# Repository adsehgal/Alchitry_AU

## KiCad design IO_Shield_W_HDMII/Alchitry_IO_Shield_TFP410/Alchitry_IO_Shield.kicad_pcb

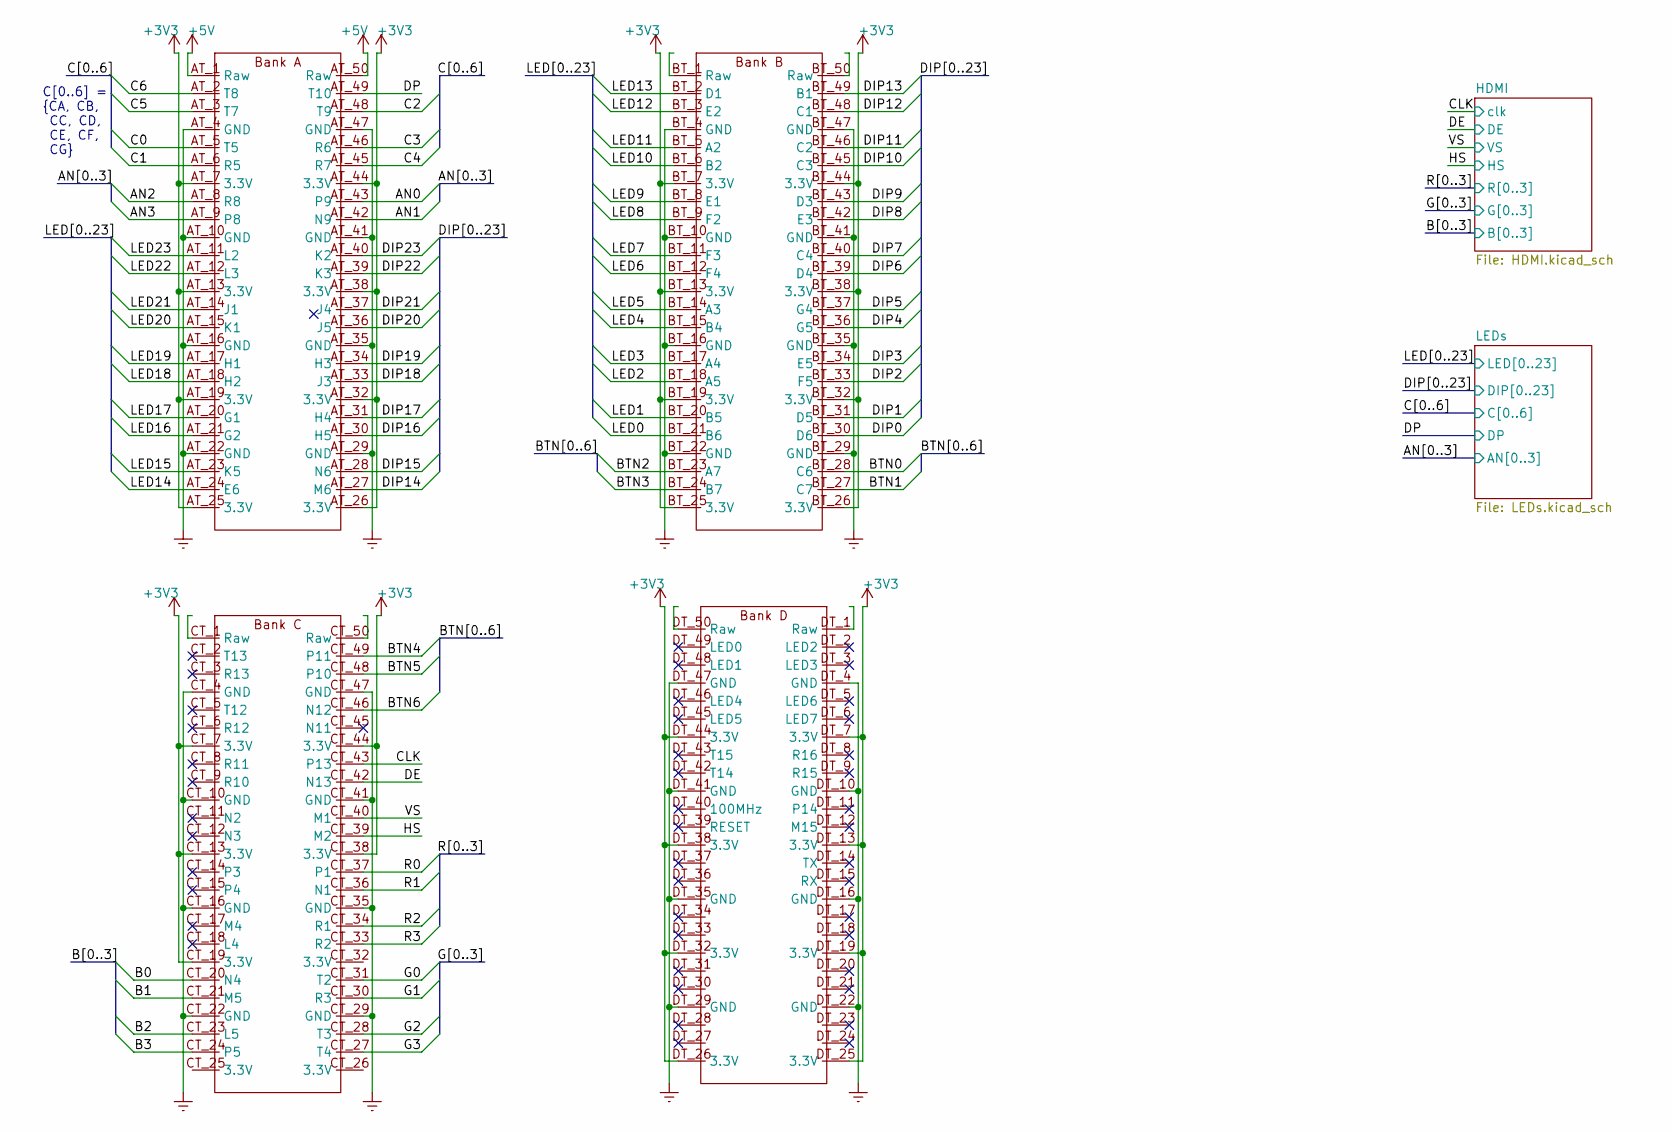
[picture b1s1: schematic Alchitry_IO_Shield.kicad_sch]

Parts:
U0: boardmezzanine_new; Alchitry_Top_Bottom

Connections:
+3V3: U0.AB_7, U0.AB_13, U0.AB_19, U0.AB_25, U0.AB_26, U0.AB_32, U0.AB_38, U0.AB_44, U0.AT_7 (3.3V), U0.AT_13 (3.3V), U0.AT_19 (3.3V), U0.AT_25 (3.3V), U0.AT_26 (3.3V), U0.AT_32 (3.3V), U0.AT_38 (3.3V), U0.AT_44 (3.3V), U0.BB_7, U0.BB_13, U0.BB_19, U0.BB_25, U0.BB_26, U0.BB_32, U0.BB_38, U0.BB_44, U0.BT_7 (3.3V), U0.BT_13 (3.3V), U0.BT_19 (3.3V), U0.BT_25 (3.3V), U0.BT_26 (3.3V), U0.BT_32 (3.3V), U0.BT_38 (3.3V), U0.BT_44 (3.3V), U0.CB_7, U0.CB_13, U0.CB_19, U0.CB_38, U0.CB_44, U0.CT_7 (3.3V), U0.CT_13 (3.3V), U0.CT_19 (3.3V), U0.CT_38 (3.3V), U0.CT_44 (3.3V), U0.DB_7, U0.DB_13, U0.DB_19, U0.DB_25, U0.DB_26, U0.DB_32, U0.DB_38, U0.DB_44, U0.DT_7 (3.3V), U0.DT_13 (3.3V), U0.DT_19 (3.3V), U0.DT_25 (3.3V), U0.DT_26 (3.3V), U0.DT_32 (3.3V), U0.DT_38 (3.3V), U0.DT_44 (3.3V); also elsewhere on the board
+5V: U0.AB_1, U0.AB_50, U0.AT_1 (Raw), U0.AT_50 (Raw); also elsewhere on the board
/AN0: U0.AB_43, U0.AT_43 (P9); also elsewhere on the board
/AN1: U0.AB_42, U0.AT_42 (N9); also elsewhere on the board
/AN2: U0.AB_8, U0.AT_8 (R8); also elsewhere on the board
/AN3: U0.AB_9, U0.AT_9 (P8); also elsewhere on the board
/B0: U0.CB_20, U0.CT_20 (N4); also elsewhere on the board
/B1: U0.CB_21, U0.CT_21 (M5); also elsewhere on the board
/B2: U0.CB_23, U0.CT_23 (L5); also elsewhere on the board
/B3: U0.CB_24, U0.CT_24 (P5); also elsewhere on the board
/BTN0: U0.BB_28, U0.BT_28 (C6)
/BTN1: U0.BB_27, U0.BT_27 (C7)
/BTN2: U0.BB_23, U0.BT_23 (A7)
/BTN3: U0.BB_24, U0.BT_24 (B7)
/BTN4: U0.CB_49, U0.CT_49 (P11)
/BTN5: U0.CB_48, U0.CT_48 (P10)
/BTN6: U0.CB_46, U0.CT_46 (N12)
/C0: U0.AB_5, U0.AT_5 (T5); also elsewhere on the board
/C1: U0.AB_6, U0.AT_6 (R5); also elsewhere on the board
/C2: U0.AB_48, U0.AT_48 (T9); also elsewhere on the board
/C3: U0.AB_46, U0.AT_46 (R6); also elsewhere on the board
/C4: U0.AB_45, U0.AT_45 (R7); also elsewhere on the board
/C5: U0.AB_3, U0.AT_3 (T7); also elsewhere on the board
/C6: U0.AB_2, U0.AT_2 (T8); also elsewhere on the board
/CLK: U0.CB_43, U0.CT_43 (P13); also elsewhere on the board
/DE: U0.CB_42, U0.CT_42 (N13); also elsewhere on the board
/DIP0: U0.BB_30, U0.BT_30 (D6); also elsewhere on the board
/DIP1: U0.BB_31, U0.BT_31 (D5); also elsewhere on the board
/DIP2: U0.BB_33, U0.BT_33 (F5); also elsewhere on the board
/DIP3: U0.BB_34, U0.BT_34 (E5); also elsewhere on the board
/DIP4: U0.BB_36, U0.BT_36 (G5); also elsewhere on the board
/DIP5: U0.BB_37, U0.BT_37 (G4); also elsewhere on the board
/DIP6: U0.BB_39, U0.BT_39 (D4); also elsewhere on the board
/DIP7: U0.BB_40, U0.BT_40 (C4); also elsewhere on the board
/DIP8: U0.BB_42, U0.BT_42 (E3); also elsewhere on the board
/DIP9: U0.BB_43, U0.BT_43 (D3); also elsewhere on the board
/DIP10: U0.BB_45, U0.BT_45 (C3); also elsewhere on the board
/DIP11: U0.BB_46, U0.BT_46 (C2); also elsewhere on the board
/DIP12: U0.BB_48, U0.BT_48 (C1); also elsewhere on the board
/DIP13: U0.BB_49, U0.BT_49 (B1); also elsewhere on the board
/DIP14: U0.AB_27, U0.AT_27 (M6); also elsewhere on the board
/DIP15: U0.AB_28, U0.AT_28 (N6); also elsewhere on the board
/DIP16: U0.AB_30, U0.AT_30 (H5); also elsewhere on the board
/DIP17: U0.AB_31, U0.AT_31 (H4); also elsewhere on the board
/DIP18: U0.AB_33, U0.AT_33 (J3); also elsewhere on the board
/DIP19: U0.AB_34, U0.AT_34 (H3); also elsewhere on the board
/DIP20: U0.AB_36, U0.AT_36 (J5); also elsewhere on the board
/DIP21: U0.AB_37, U0.AT_37 (J4); also elsewhere on the board
/DIP22: U0.AB_39, U0.AT_39 (K3); also elsewhere on the board
/DIP23: U0.AB_40, U0.AT_40 (K2); also elsewhere on the board
/DP: U0.AB_49, U0.AT_49 (T10)
/G0: U0.CB_31, U0.CT_31 (T2); also elsewhere on the board
/G1: U0.CB_30, U0.CT_30 (R3); also elsewhere on the board
/G2: U0.CB_28, U0.CT_28 (T3); also elsewhere on the board
/G3: U0.CB_27, U0.CT_27 (T4); also elsewhere on the board
/HS: U0.CB_39, U0.CT_39 (M2); also elsewhere on the board
/LED0: U0.BB_21, U0.BT_21 (B6); also elsewhere on the board
/LED1: U0.BB_20, U0.BT_20 (B5); also elsewhere on the board
/LED2: U0.BB_18, U0.BT_18 (A5); also elsewhere on the board
/LED3: U0.BB_17, U0.BT_17 (A4); also elsewhere on the board
/LED4: U0.BB_15, U0.BT_15 (B4); also elsewhere on the board
/LED5: U0.BB_14, U0.BT_14 (A3); also elsewhere on the board
/LED6: U0.BB_12, U0.BT_12 (F4); also elsewhere on the board
/LED7: U0.BB_11, U0.BT_11 (F3); also elsewhere on the board
/LED8: U0.BB_9, U0.BT_9 (F2); also elsewhere on the board
/LED9: U0.BB_8, U0.BT_8 (E1); also elsewhere on the board
/LED10: U0.BB_6, U0.BT_6 (B2); also elsewhere on the board
/LED11: U0.BB_5, U0.BT_5 (A2); also elsewhere on the board
/LED12: U0.BB_3, U0.BT_3 (E2); also elsewhere on the board
/LED13: U0.BB_2, U0.BT_2 (D1); also elsewhere on the board
/LED14: U0.AB_24, U0.AT_24 (E6); also elsewhere on the board
/LED15: U0.AB_23, U0.AT_23 (K5); also elsewhere on the board
/LED16: U0.AB_21, U0.AT_21 (G2); also elsewhere on the board
/LED17: U0.AB_20, U0.AT_20 (G1); also elsewhere on the board
/LED18: U0.AB_18, U0.AT_18 (H2); also elsewhere on the board
/LED19: U0.AB_17, U0.AT_17 (H1); also elsewhere on the board
/LED20: U0.AB_15, U0.AT_15 (K1); also elsewhere on the board
/LED21: U0.AB_14, U0.AT_14 (J1); also elsewhere on the board
/LED22: U0.AB_12, U0.AT_12 (L3); also elsewhere on the board
/LED23: U0.AB_11, U0.AT_11 (L2); also elsewhere on the board
/R0: U0.CB_37, U0.CT_37 (P1); also elsewhere on the board
/R1: U0.CB_36, U0.CT_36 (N1); also elsewhere on the board
/R2: U0.CB_34, U0.CT_34 (R1); also elsewhere on the board
/R3: U0.CB_33, U0.CT_33 (R2); also elsewhere on the board
/VS: U0.CB_40, U0.CT_40 (M1); also elsewhere on the board
GNDREF: U0.AB_4, U0.AB_10, U0.AB_16, U0.AB_22, U0.AB_29, U0.AB_35, U0.AB_41, U0.AB_47, U0.AT_4 (GND), U0.AT_10 (GND), U0.AT_16 (GND), U0.AT_22 (GND), U0.AT_29 (GND), U0.AT_35 (GND), U0.AT_41 (GND), U0.AT_47 (GND), U0.BB_4, U0.BB_10, U0.BB_16, U0.BB_22, U0.BB_29, U0.BB_35, U0.BB_41, U0.BB_47, U0.BT_4 (GND), U0.BT_10 (GND), U0.BT_16 (GND), U0.BT_22 (GND), U0.BT_29 (GND), U0.BT_35 (GND), U0.BT_41 (GND), U0.BT_47 (GND), U0.CB_4, U0.CB_10, U0.CB_16, U0.CB_22, U0.CB_29, U0.CB_35, U0.CB_41, U0.CB_47, U0.CT_4 (GND), U0.CT_10 (GND), U0.CT_16 (GND), U0.CT_22 (GND), U0.CT_29 (GND), U0.CT_35 (GND), U0.CT_41 (GND), U0.CT_47 (GND), U0.DB_4, U0.DB_10, U0.DB_16, U0.DB_22, U0.DB_29, U0.DB_35, U0.DB_41, U0.DB_47, U0.DT_4 (GND), U0.DT_10 (GND), U0.DT_16 (GND), U0.DT_22 (GND), U0.DT_29 (GND), U0.DT_35 (GND), U0.DT_41 (GND), U0.DT_47 (GND); also elsewhere on the board
unnamed: U0.BB_1, U0.BT_1 (Raw)
unnamed: U0.BB_50, U0.BT_50 (Raw)
unnamed: U0.CB_1, U0.CT_1 (Raw)
unnamed: U0.CB_2, U0.CT_2 (T13)
unnamed: U0.CB_3, U0.CT_3 (R13)
unnamed: U0.CB_5, U0.CT_5 (T12)
unnamed: U0.CB_6, U0.CT_6 (R12)
unnamed: U0.CB_8, U0.CT_8 (R11)
unnamed: U0.CB_9, U0.CT_9 (R10)
unnamed: U0.CB_11, U0.CT_11 (N2)
unnamed: U0.CB_12, U0.CT_12 (N3)
unnamed: U0.CB_14, U0.CT_14 (P3)
unnamed: U0.CB_15, U0.CT_15 (P4)
unnamed: U0.CB_17, U0.CT_17 (M4)
unnamed: U0.CB_18, U0.CT_18 (L4)
unnamed: U0.CB_25, U0.CT_25 (3.3V)
unnamed: U0.CB_26, U0.CT_26 (3.3V)
unnamed: U0.CB_32, U0.CT_32 (3.3V)
unnamed: U0.CB_45, U0.CT_45 (N11)
unnamed: U0.CB_50, U0.CT_50 (Raw)
unnamed: U0.DB_1, U0.DT_1 (Raw)
unnamed: U0.DB_2, U0.DT_2 (LED2)
unnamed: U0.DB_3, U0.DT_3 (LED3)
unnamed: U0.DB_5, U0.DT_5 (LED6)
unnamed: U0.DB_6, U0.DT_6 (LED7)
unnamed: U0.DB_8, U0.DT_8 (R16)
unnamed: U0.DB_9, U0.DT_9 (R15)
unnamed: U0.DB_11, U0.DT_11 (P14)
unnamed: U0.DB_12, U0.DT_12 (M15)
unnamed: U0.DB_14, U0.DT_14 (TX)
unnamed: U0.DB_15, U0.DT_15 (RX)
unnamed: U0.DB_17, U0.DT_17
unnamed: U0.DB_18, U0.DT_18
unnamed: U0.DB_20, U0.DT_20
unnamed: U0.DB_21, U0.DT_21
unnamed: U0.DB_23, U0.DT_23
unnamed: U0.DB_24, U0.DT_24
unnamed: U0.DB_27, U0.DT_27
unnamed: U0.DB_28, U0.DT_28
unnamed: U0.DB_30, U0.DT_30
unnamed: U0.DB_31, U0.DT_31
unnamed: U0.DB_33, U0.DT_33
unnamed: U0.DB_34, U0.DT_34
unnamed: U0.DB_36, U0.DT_36
unnamed: U0.DB_37, U0.DT_37
unnamed: U0.DB_39, U0.DT_39 (RESET)
unnamed: U0.DB_40, U0.DT_40 (100MHz)
unnamed: U0.DB_42, U0.DT_42 (T14)
unnamed: U0.DB_43, U0.DT_43 (T15)
unnamed: U0.DB_45, U0.DT_45 (LED5)
unnamed: U0.DB_46, U0.DT_46 (LED4)
unnamed: U0.DB_48, U0.DT_48 (LED1)
unnamed: U0.DB_49, U0.DT_49 (LED0)
unnamed: U0.DB_50, U0.DT_50 (Raw)

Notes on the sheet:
C[0..6] = {CA, CB, CC, CD, CE, CF, CG}

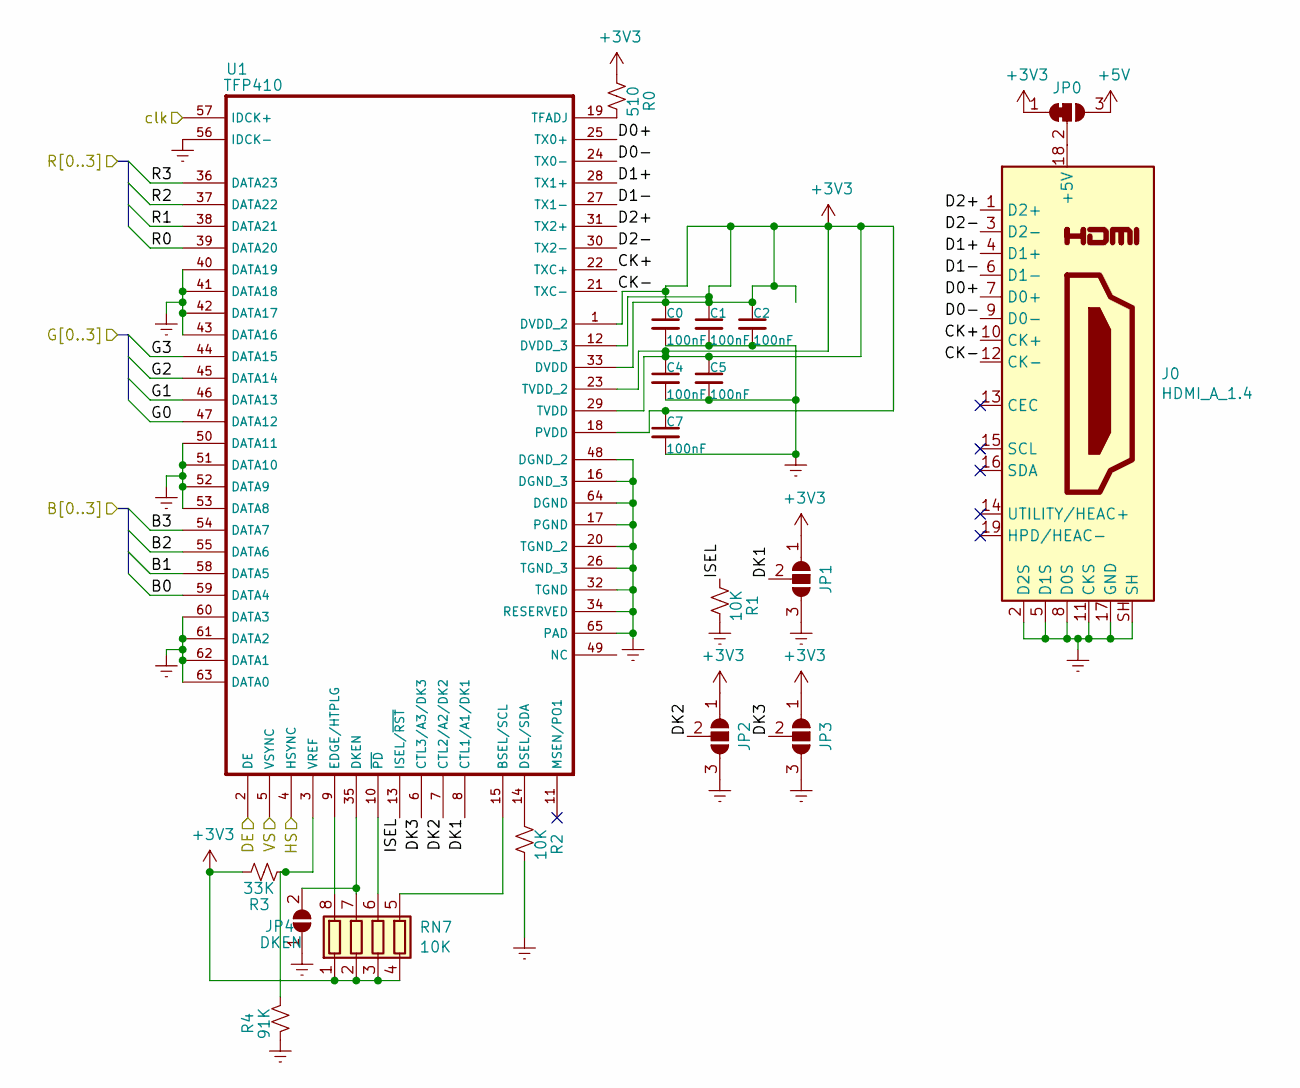
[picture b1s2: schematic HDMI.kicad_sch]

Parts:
C0, C1, C2, C4, C5, C7: 100nF; C_0603_1608Metric_Pad1.05x0.95mm_HandSolder
J0: HDMI_A_1.4; HDMI
JP0: V_Sel; jumper_1_2_bridged
JP1: DK1; jumper_unbridged
JP2: DK2; jumper_unbridged
JP3: DK3; jumper_unbridged
JP4: DKEN; Jumper_2_Pin_Unbridged
R0: 510; R_0603_1608Metric_Pad1.05x0.95mm_HandSolder
R1, R2: 10K; R_0603_1608Metric
R3: 33K; R_0603_1608Metric
R4: 91K; R_0603_1608Metric
RN7: 10K; R_Array_Concave_4x0603
U1: TFP410; HTQFP-64-1EP_10x10mm_P0.5mm_EP8x8mm_Mask4.4x4.4mm_ThermalVi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

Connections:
+3V3: C0.1, C1.1, C2.1, C4.1, C5.1, C7.1, JP0.1 (A), JP1.1 (A), JP2.1 (A), JP3.1 (A), R0.1, R3.2, RN7.1 (R1.1), RN7.2 (R2.1), RN7.3 (R3.1), RN7.4 (R4.1), U1.1 (DVDD_2), U1.12 (DVDD_3), U1.18 (PVDD), U1.23 (TVDD_2), U1.29 (TVDD), U1.33 (DVDD); also elsewhere on the board
+5V: JP0.3 (B); also elsewhere on the board
/B0: U1.59 (DATA4); also elsewhere on the board
/B1: U1.58 (DATA5); also elsewhere on the board
/B2: U1.55 (DATA6); also elsewhere on the board
/B3: U1.54 (DATA7); also elsewhere on the board
/CLK: U1.57 (IDCK+); also elsewhere on the board
/DE: U1.2 (DE); also elsewhere on the board
/G0: U1.47 (DATA12); also elsewhere on the board
/G1: U1.46 (DATA13); also elsewhere on the board
/G2: U1.45 (DATA14); also elsewhere on the board
/G3: U1.44 (DATA15); also elsewhere on the board
/HDMI/CK+: J0.10 (CK+), U1.22 (TXC+)
/HDMI/CK-: J0.12 (CK-), U1.21 (TXC-)
/HDMI/D0+: J0.7 (D0+), U1.25 (TX0+)
/HDMI/D0-: J0.9 (D0-), U1.24 (TX0-)
/HDMI/D1+: J0.4 (D1+), U1.28 (TX1+)
/HDMI/D1-: J0.6 (D1-), U1.27 (TX1-)
/HDMI/D2+: J0.1 (D2+), U1.31 (TX2+)
/HDMI/D2-: J0.3 (D2-), U1.30 (TX2-)
/HDMI/DK1: JP1.2 (C), U1.8 (CTL1/A1/DK1)
/HDMI/DK2: JP2.2 (C), U1.7 (CTL2/A2/DK2)
/HDMI/DK3: JP3.2 (C), U1.6 (CTL3/A3/DK3)
/HDMI/ISEL: R1.1, U1.13 (ISEL/~RST)
/HS: U1.4 (HSYNC); also elsewhere on the board
/R0: U1.39 (DATA20); also elsewhere on the board
/R1: U1.38 (DATA21); also elsewhere on the board
/R2: U1.37 (DATA22); also elsewhere on the board
/R3: U1.36 (DATA23); also elsewhere on the board
/VS: U1.5 (VSYNC); also elsewhere on the board
GNDREF: C0.2, C1.2, C2.2, C4.2, C5.2, C7.2, J0.2 (D2S), J0.5 (D1S), J0.8 (D0S), J0.11 (CKS), J0.17 (GND), J0.SH, JP1.3 (B), JP2.3 (B), JP3.3 (B), JP4.1 (A), R1.2, R2.2, R4.2, U1.16 (DGND_3), U1.17 (PGND), U1.20 (TGND_2), U1.26 (TGND_3), U1.32 (TGND), U1.34 (RESERVED), U1.40 (DATA19), U1.41 (DATA18), U1.42 (DATA17), U1.43 (DATA16), U1.48 (DGND_2), U1.50 (DATA11), U1.51 (DATA10), U1.52 (DATA9), U1.53 (DATA8), U1.56 (IDCK-), U1.60 (DATA3), U1.61 (DATA2), U1.62 (DATA1), U1.63 (DATA0), U1.64 (DGND), U1.65 (PAD); also elsewhere on the board
unnamed: J0.18 (+5V), JP0.2 (C)
unnamed: JP4.2 (B), RN7.7 (R2.2), U1.35 (DKEN)
unnamed: R0.2, U1.19 (TFADJ)
unnamed: R2.1, U1.14 (DSEL/SDA)
unnamed: R3.1, R4.1, U1.3 (VREF)
unnamed: RN7.5 (R4.2), U1.15 (BSEL/SCL)
unnamed: RN7.6 (R3.2), U1.10 (~PD)
unnamed: RN7.8 (R1.2), U1.9 (EDGE/HTPLG)

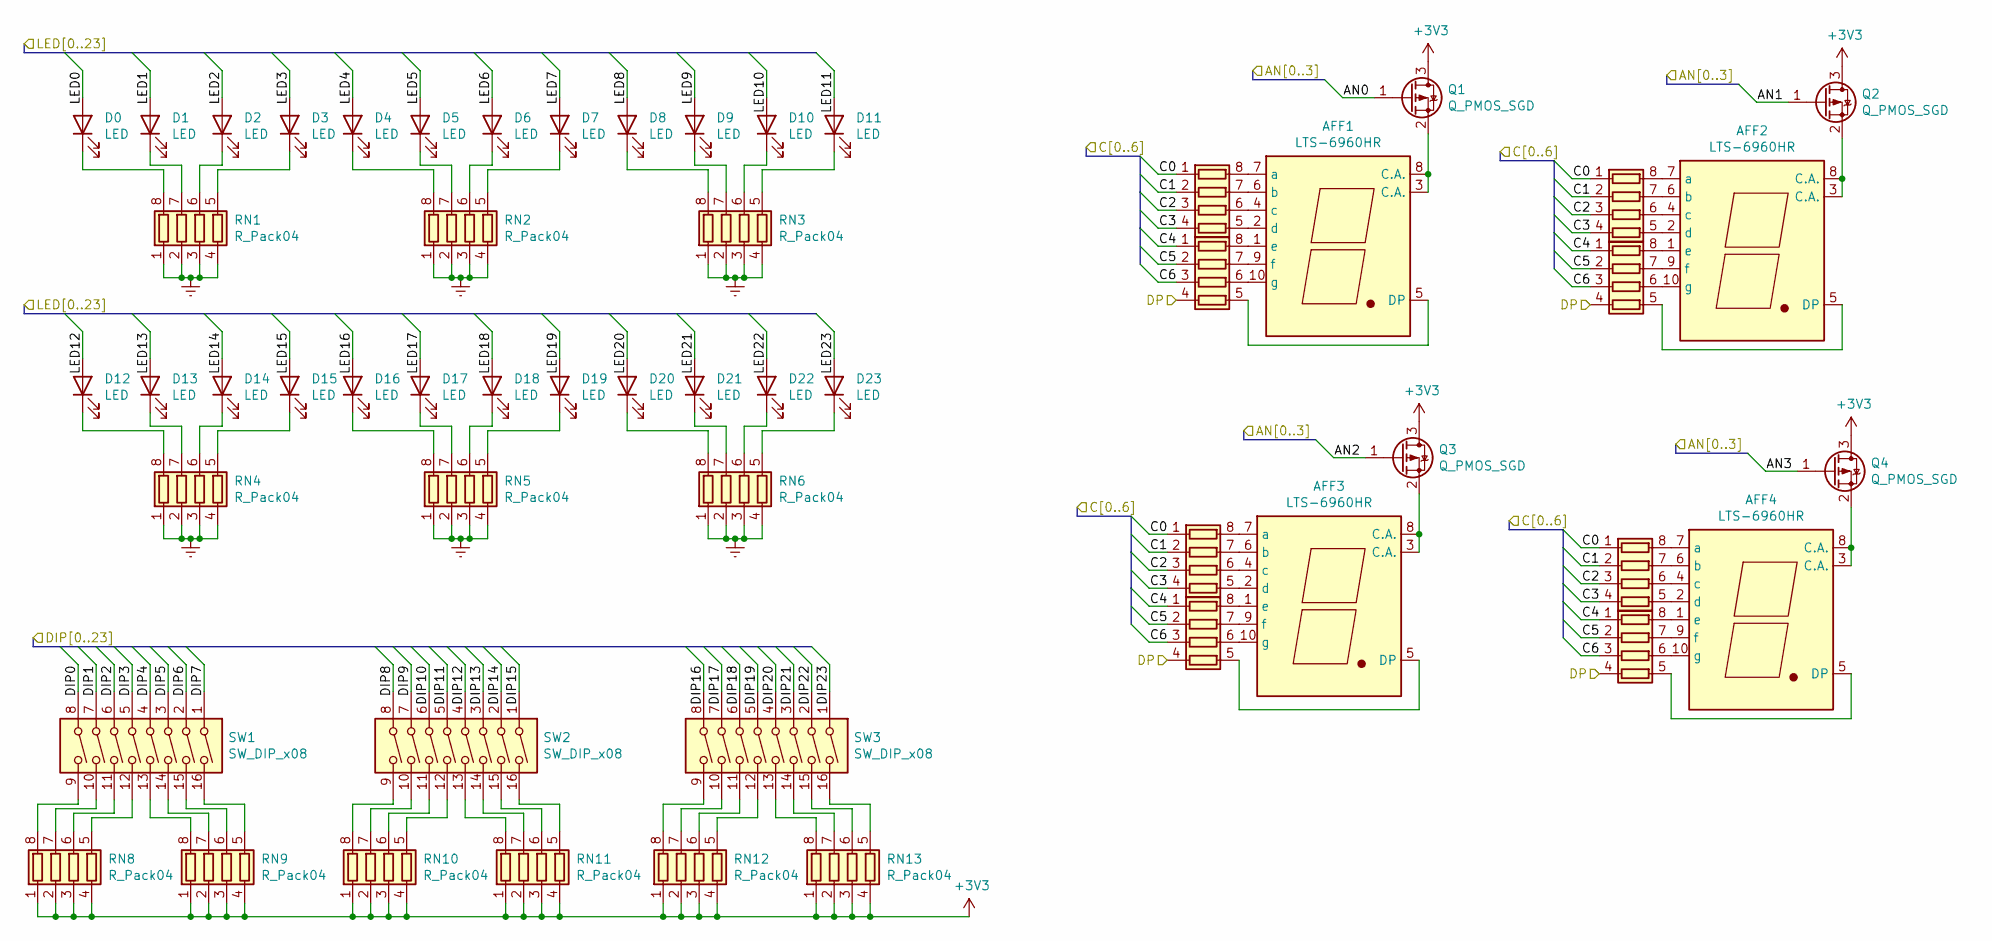
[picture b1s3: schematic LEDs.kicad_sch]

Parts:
AFF1, AFF2, AFF3, AFF4: LTS-6960HR; KCSC02-136
D0, D1, D2, D3, D4, D5, D6, D7, D8, D9, D10, D11, D12, D13, D14, D15, D16, D17, D18, D19, D20, D21, D22, D23: LED; LED_0603_1608Metric_Pad1.05x0.95mm_HandSolder
Q1, Q2, Q3, Q4: Q_PMOS_SGD; SOT-23
RN1, RN2, RN3, RN4, RN5, RN6, RN8, RN9, RN10, RN11, RN12, RN13, RN14, RN15, RN16, RN17, RN18, RN19, RN20, RN21: R_Pack04; R_Array_Convex_4x0603
SW1, SW2, SW3: SW_DIP_x08; SW_DIP_SPSTx08_Slide_Copal_CHS-08B_W7.62mm_P1.27mm

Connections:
+3V3: Q1.3 (D), Q2.3 (D), Q3.3 (D), Q4.3 (D), RN8.1 (R1.1), RN8.2 (R2.1), RN8.3 (R3.1), RN8.4 (R4.1), RN9.1 (R1.1), RN9.2 (R2.1), RN9.3 (R3.1), RN9.4 (R4.1), RN10.1 (R1.1), RN10.2 (R2.1), RN10.3 (R3.1), RN10.4 (R4.1), RN11.1 (R1.1), RN11.2 (R2.1), RN11.3 (R3.1), RN11.4 (R4.1), RN12.1 (R1.1), RN12.2 (R2.1), RN12.3 (R3.1), RN12.4 (R4.1), RN13.1 (R1.1), RN13.2 (R2.1), RN13.3 (R3.1), RN13.4 (R4.1); also elsewhere on the board
/AN0: Q1.1 (G); also elsewhere on the board
/AN1: Q2.1 (G); also elsewhere on the board
/AN2: Q3.1 (G); also elsewhere on the board
/AN3: Q4.1 (G); also elsewhere on the board
/C0: RN14.1 (R1.1), RN15.1 (R1.1), RN18.1 (R1.1), RN19.1 (R1.1); also elsewhere on the board
/C1: RN14.2 (R2.1), RN15.2 (R2.1), RN18.2 (R2.1), RN19.2 (R2.1); also elsewhere on the board
/C2: RN14.3 (R3.1), RN15.3 (R3.1), RN18.3 (R3.1), RN19.3 (R3.1); also elsewhere on the board
/C3: RN14.4 (R4.1), RN15.4 (R4.1), RN18.4 (R4.1), RN19.4 (R4.1); also elsewhere on the board
/C4: RN16.1 (R1.1), RN17.1 (R1.1), RN20.1 (R1.1), RN21.1 (R1.1); also elsewhere on the board
/C5: RN16.2 (R2.1), RN17.2 (R2.1), RN20.2 (R2.1), RN21.2 (R2.1); also elsewhere on the board
/C6: RN16.3 (R3.1), RN17.3 (R3.1), RN20.3 (R3.1), RN21.3 (R3.1); also elsewhere on the board
/DIP0: SW1.8; also elsewhere on the board
/DIP1: SW1.7; also elsewhere on the board
/DIP2: SW1.6; also elsewhere on the board
/DIP3: SW1.5; also elsewhere on the board
/DIP4: SW1.4; also elsewhere on the board
/DIP5: SW1.3; also elsewhere on the board
/DIP6: SW1.2; also elsewhere on the board
/DIP7: SW1.1; also elsewhere on the board
/DIP8: SW2.8; also elsewhere on the board
/DIP9: SW2.7; also elsewhere on the board
/DIP10: SW2.6; also elsewhere on the board
/DIP11: SW2.5; also elsewhere on the board
/DIP12: SW2.4; also elsewhere on the board
/DIP13: SW2.3; also elsewhere on the board
/DIP14: SW2.2; also elsewhere on the board
/DIP15: SW2.1; also elsewhere on the board
/DIP16: SW3.8; also elsewhere on the board
/DIP17: SW3.7; also elsewhere on the board
/DIP18: SW3.6; also elsewhere on the board
/DIP19: SW3.5; also elsewhere on the board
/DIP20: SW3.4; also elsewhere on the board
/DIP21: SW3.3; also elsewhere on the board
/DIP22: SW3.2; also elsewhere on the board
/DIP23: SW3.1; also elsewhere on the board
/LED0: D0.2 (A); also elsewhere on the board
/LED1: D1.2 (A); also elsewhere on the board
/LED2: D2.2 (A); also elsewhere on the board
/LED3: D3.2 (A); also elsewhere on the board
/LED4: D4.2 (A); also elsewhere on the board
/LED5: D5.2 (A); also elsewhere on the board
/LED6: D6.2 (A); also elsewhere on the board
/LED7: D7.2 (A); also elsewhere on the board
/LED8: D8.2 (A); also elsewhere on the board
/LED9: D9.2 (A); also elsewhere on the board
/LED10: D10.2 (A); also elsewhere on the board
/LED11: D11.2 (A); also elsewhere on the board
/LED12: D12.2 (A); also elsewhere on the board
/LED13: D13.2 (A); also elsewhere on the board
/LED14: D14.2 (A); also elsewhere on the board
/LED15: D15.2 (A); also elsewhere on the board
/LED16: D16.2 (A); also elsewhere on the board
/LED17: D17.2 (A); also elsewhere on the board
/LED18: D18.2 (A); also elsewhere on the board
/LED19: D19.2 (A); also elsewhere on the board
/LED20: D20.2 (A); also elsewhere on the board
/LED21: D21.2 (A); also elsewhere on the board
/LED22: D22.2 (A); also elsewhere on the board
/LED23: D23.2 (A); also elsewhere on the board
/LEDs/DP: RN16.4 (R4.1), RN17.4 (R4.1), RN20.4 (R4.1), RN21.4 (R4.1)
GNDREF: RN1.1 (R1.1), RN1.2 (R2.1), RN1.3 (R3.1), RN1.4 (R4.1), RN2.1 (R1.1), RN2.2 (R2.1), RN2.3 (R3.1), RN2.4 (R4.1), RN3.1 (R1.1), RN3.2 (R2.1), RN3.3 (R3.1), RN3.4 (R4.1), RN4.1 (R1.1), RN4.2 (R2.1), RN4.3 (R3.1), RN4.4 (R4.1), RN5.1 (R1.1), RN5.2 (R2.1), RN5.3 (R3.1), RN5.4 (R4.1), RN6.1 (R1.1), RN6.2 (R2.1), RN6.3 (R3.1), RN6.4 (R4.1); also elsewhere on the board
unnamed: AFF1.1 (e), RN16.8 (R1.2)
unnamed: AFF1.2 (d), RN14.5 (R4.2)
unnamed: AFF1.3 (C.A.), AFF1.8 (C.A.), Q1.2 (S)
unnamed: AFF1.4 (c), RN14.6 (R3.2)
unnamed: AFF1.5 (DP), RN16.5 (R4.2)
unnamed: AFF1.6 (b), RN14.7 (R2.2)
unnamed: AFF1.7 (a), RN14.8 (R1.2)
unnamed: AFF1.9 (f), RN16.7 (R2.2)
unnamed: AFF1.10 (g), RN16.6 (R3.2)
unnamed: AFF2.1 (e), RN17.8 (R1.2)
unnamed: AFF2.2 (d), RN15.5 (R4.2)
unnamed: AFF2.3 (C.A.), AFF2.8 (C.A.), Q2.2 (S)
unnamed: AFF2.4 (c), RN15.6 (R3.2)
unnamed: AFF2.5 (DP), RN17.5 (R4.2)
unnamed: AFF2.6 (b), RN15.7 (R2.2)
unnamed: AFF2.7 (a), RN15.8 (R1.2)
unnamed: AFF2.9 (f), RN17.7 (R2.2)
unnamed: AFF2.10 (g), RN17.6 (R3.2)
unnamed: AFF3.1 (e), RN20.8 (R1.2)
unnamed: AFF3.2 (d), RN18.5 (R4.2)
unnamed: AFF3.3 (C.A.), AFF3.8 (C.A.), Q3.2 (S)
unnamed: AFF3.4 (c), RN18.6 (R3.2)
unnamed: AFF3.5 (DP), RN20.5 (R4.2)
unnamed: AFF3.6 (b), RN18.7 (R2.2)
unnamed: AFF3.7 (a), RN18.8 (R1.2)
unnamed: AFF3.9 (f), RN20.7 (R2.2)
unnamed: AFF3.10 (g), RN20.6 (R3.2)
unnamed: AFF4.1 (e), RN21.8 (R1.2)
unnamed: AFF4.2 (d), RN19.5 (R4.2)
unnamed: AFF4.3 (C.A.), AFF4.8 (C.A.), Q4.2 (S)
unnamed: AFF4.4 (c), RN19.6 (R3.2)
unnamed: AFF4.5 (DP), RN21.5 (R4.2)
unnamed: AFF4.6 (b), RN19.7 (R2.2)
unnamed: AFF4.7 (a), RN19.8 (R1.2)
unnamed: AFF4.9 (f), RN21.7 (R2.2)
unnamed: AFF4.10 (g), RN21.6 (R3.2)
unnamed: D0.1 (K), RN1.8 (R1.2)
unnamed: D1.1 (K), RN1.7 (R2.2)
unnamed: D2.1 (K), RN1.6 (R3.2)
unnamed: D3.1 (K), RN1.5 (R4.2)
unnamed: D4.1 (K), RN2.8 (R1.2)
unnamed: D5.1 (K), RN2.7 (R2.2)
unnamed: D6.1 (K), RN2.6 (R3.2)
unnamed: D7.1 (K), RN2.5 (R4.2)
unnamed: D8.1 (K), RN3.8 (R1.2)
unnamed: D9.1 (K), RN3.7 (R2.2)
unnamed: D10.1 (K), RN3.6 (R3.2)
unnamed: D11.1 (K), RN3.5 (R4.2)
unnamed: D12.1 (K), RN4.8 (R1.2)
unnamed: D13.1 (K), RN4.7 (R2.2)
unnamed: D14.1 (K), RN4.6 (R3.2)
unnamed: D15.1 (K), RN4.5 (R4.2)
unnamed: D16.1 (K), RN5.8 (R1.2)
unnamed: D17.1 (K), RN5.7 (R2.2)
unnamed: D18.1 (K), RN5.6 (R3.2)
unnamed: D19.1 (K), RN5.5 (R4.2)
unnamed: D20.1 (K), RN6.8 (R1.2)
unnamed: D21.1 (K), RN6.7 (R2.2)
unnamed: D22.1 (K), RN6.6 (R3.2)
unnamed: D23.1 (K), RN6.5 (R4.2)
unnamed: RN8.5 (R4.2), SW1.12
unnamed: RN8.6 (R3.2), SW1.11
unnamed: RN8.7 (R2.2), SW1.10
unnamed: RN8.8 (R1.2), SW1.9
unnamed: RN9.5 (R4.2), SW1.16
unnamed: RN9.6 (R3.2), SW1.15
unnamed: RN9.7 (R2.2), SW1.14
unnamed: RN9.8 (R1.2), SW1.13
unnamed: RN10.5 (R4.2), SW2.12
unnamed: RN10.6 (R3.2), SW2.11
unnamed: RN10.7 (R2.2), SW2.10
unnamed: RN10.8 (R1.2), SW2.9
unnamed: RN11.5 (R4.2), SW2.16
unnamed: RN11.6 (R3.2), SW2.15
unnamed: RN11.7 (R2.2), SW2.14
unnamed: RN11.8 (R1.2), SW2.13
unnamed: RN12.5 (R4.2), SW3.12
unnamed: RN12.6 (R3.2), SW3.11
unnamed: RN12.7 (R2.2), SW3.10
unnamed: RN12.8 (R1.2), SW3.9
unnamed: RN13.5 (R4.2), SW3.16
unnamed: RN13.6 (R3.2), SW3.15
unnamed: RN13.7 (R2.2), SW3.14
unnamed: RN13.8 (R1.2), SW3.13

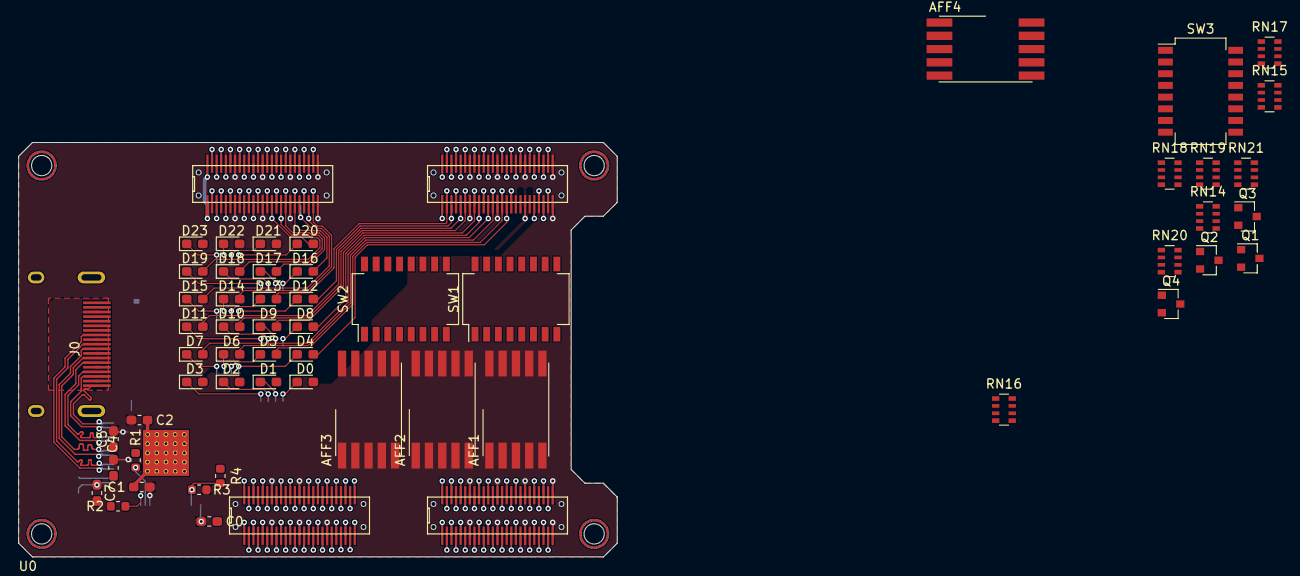
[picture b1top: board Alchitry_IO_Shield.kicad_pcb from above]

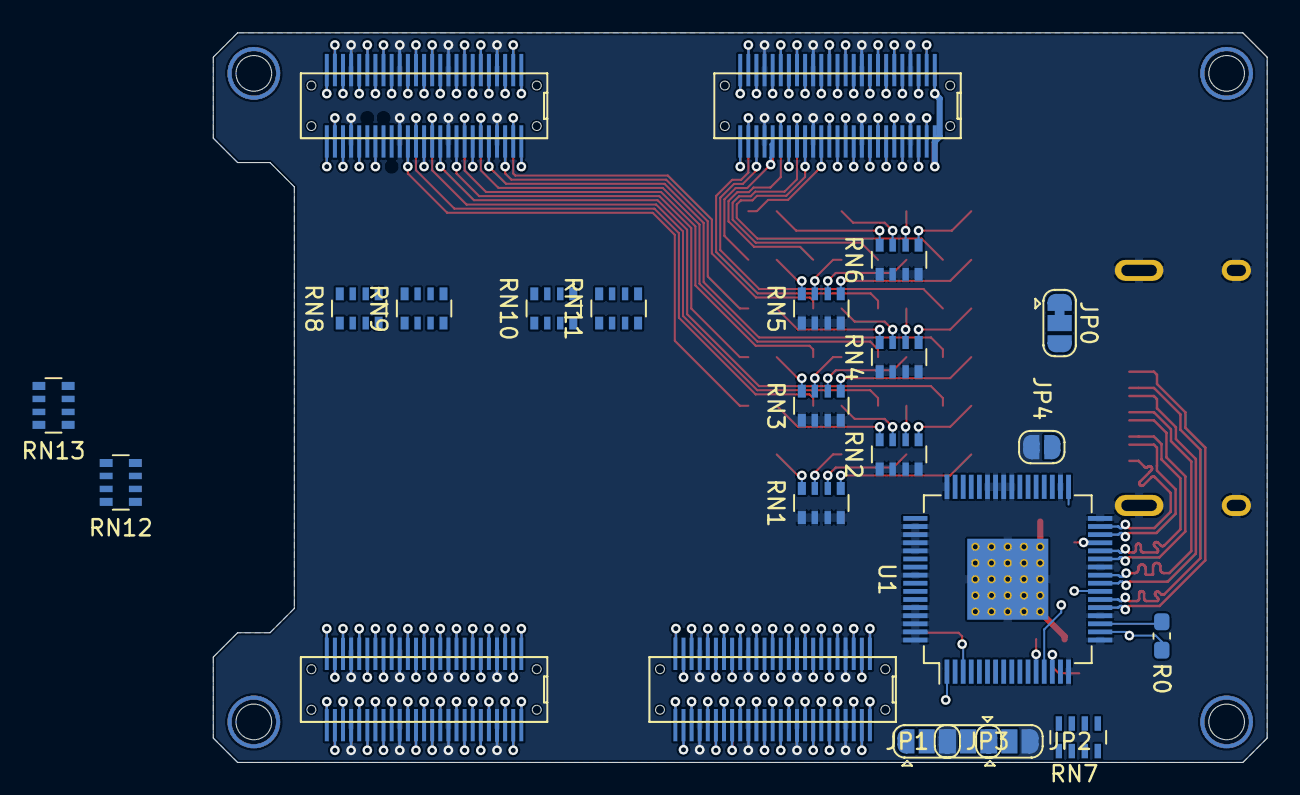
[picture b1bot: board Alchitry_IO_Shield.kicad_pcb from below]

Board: 2 copper layers, 65.0 x 45.0 mm, 75 parts (20 on the bottom side), 245 nets.
